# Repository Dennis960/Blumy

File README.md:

# Blumy

- A smart soil moisture sensor

## Project Structure

- [.devcontainer](.devcontainer): Contains the configurations for the devcontainers
- [.github](.github): Contains the configuration for GitHub Actions
- [Board](Board): Contains the KiCad project for the board
- [Panel](Panel): Contains the KiCad project for the board panel. Generation of the panel is done with `KiKit`
- [Firmware](Firmware): Contains the firmware for the esp(32) sensor (uses esp-idf)
- [Pages](Pages): Contains the website for the project's showcase
- [Server](Server): Contains the website for displaying sensor data

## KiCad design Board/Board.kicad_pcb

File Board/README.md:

# This project uses KiCad 7

## Plugins:

- [Fabrication ToolKit](https://github.com/bennymeg/JLC-Plugin-for-KiCad)

## Other software

- [JLC2KiCadLib Downloader](https://github.com/TousstNicolas/JLC2KiCad_lib)
- inside Board run `JLC2KiCadLib C94599 C1525 C1525 C1527 C16780 C15195 C15525 C2297 C81598 C84256 C26082 C25905 C11702 C25744 C4109 C318884 C318884 C2827328 C146233 C6186 C778186 C5736265 C10418 C2997435 -dir lib -model_dir packages3d -footprint_lib CustomFootprints.pretty -symbol_lib_dir symbol -symbol_lib Custom_Parts`

## PCB Manufacturer

- [JLCPCB](https://jlcpcb.com/)

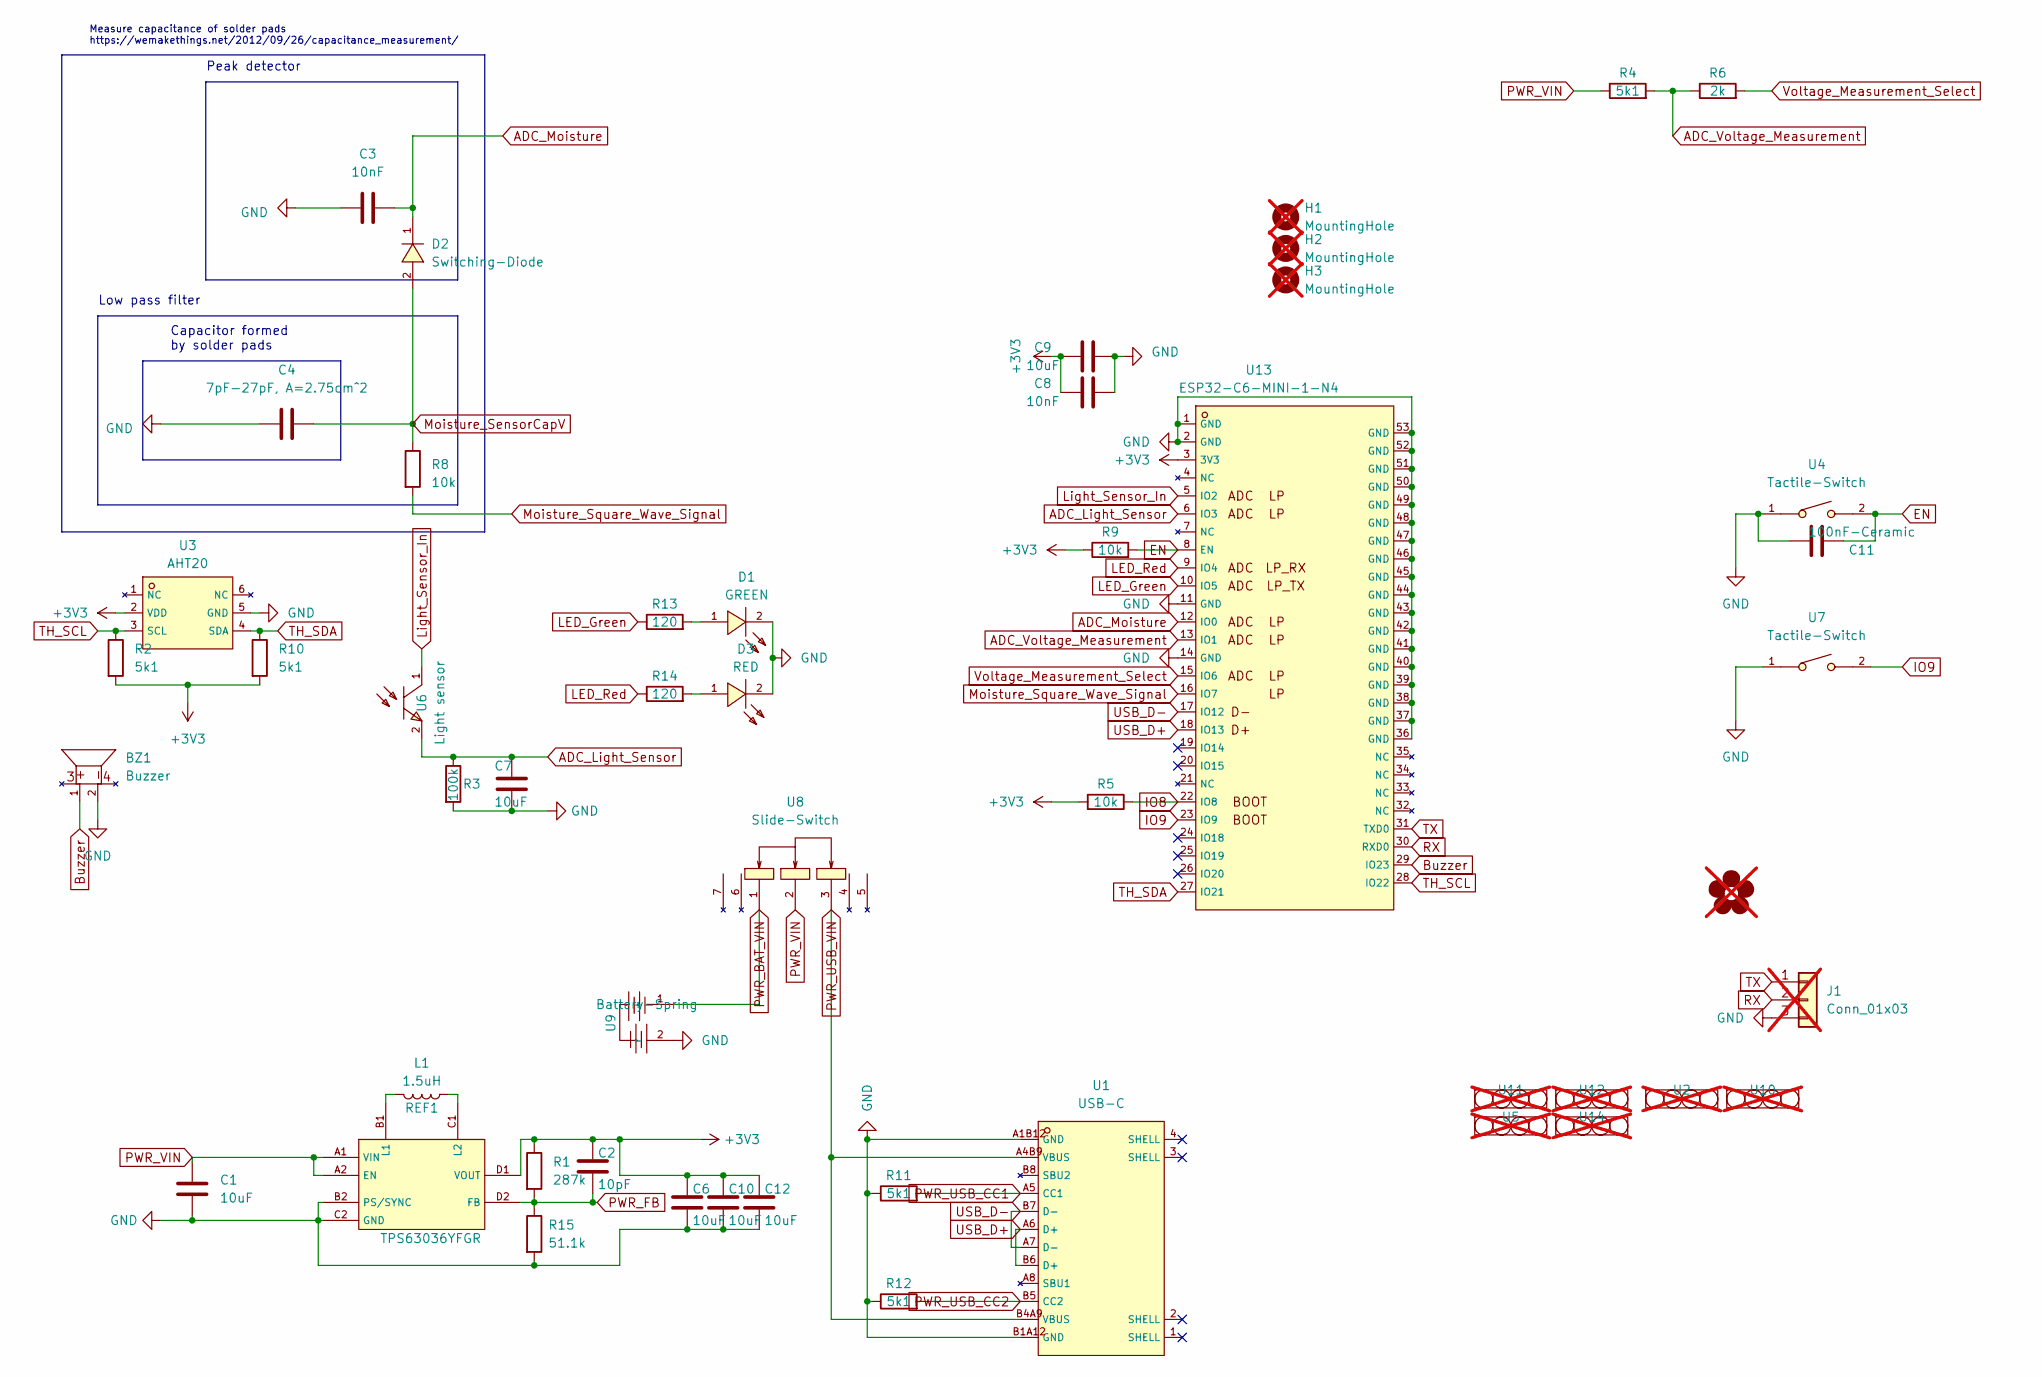
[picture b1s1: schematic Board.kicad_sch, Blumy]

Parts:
BZ1: Buzzer; BUZ-SMD_4P-L8.5-W8.5-P8.50-BR; MPN C94599; LCSC C94599
C1, C6, C7, C9, C10, C12: 10uF; C_0402_1005Metric; MPN C15525; LCSC C15525
C2: 10pF; C_0402_1005Metric; MPN C32949; LCSC C32949
C3, C8: 10nF; C_0402_1005Metric; MPN C15195; LCSC C15195
C4: 7pF-27pF, A=2.75cm^2; Sensor-Tip; MPN /
C11: 100nF-Ceramic; C_0402_1005Metric; MPN C1525; LCSC C1525
D1: GREEN; LED0805-R-RD; MPN C2297; LCSC C2297
D2: Switching-Diode; SOD-123F_L2.7-W1.6-LS3.8-RD; MPN C81598; LCSC C81598
D3: RED; LED0805-R-RD; MPN C84256; LCSC C84256
Flower1: Flower; MPN /; not fitted
H1, H2, H3: MountingHole; MountingHole_3.2mm_M3; MPN /; not fitted
J1: Conn_01x03; PinHeader_1x03_P2.54mm_Vertical_SMD; MPN /; not fitted
L1: 1.5uH; L0806; MPN C668311; LCSC C668311
R1: 287k; R_0402_1005Metric; MPN C321426; LCSC C321426
R2, R4, R10, R11, R12: 5k1; R_0402_1005Metric; MPN C25905; LCSC C25905
R3: 100k; R_0402_1005Metric; MPN C25741; LCSC C25741
R5, R8, R9: 10k; R_0402_1005Metric; MPN C25744; LCSC C25744
R6: 2k; R_0402_1005Metric; MPN C4109; LCSC C4109
R13, R14: 120; R_0402_1005Metric; MPN C25079; LCSC C25079
R15: 51.1k; R_0402_1005Metric; MPN C284602; LCSC C284602
REF1: TPS63036YFGR; DSBGA-8_L1.8-W1.1-R2-C4-P0.40-BR; MPN C283955; LCSC C283955
U1: USB-C; USB-C-SMD_G-SWITCH_GT-USB-7010EN; MPN C2997435; LCSC C2997435
U2, U5, U10, U11, U12, U14: MouseBites5mm; MPN /; not fitted
U3: AHT20; SENSOR-SMD-6_AHT20; MPN C2757850; LCSC C2757850
U4, U7: Tactile-Switch; SW-SMD_L3.9-W3.0-P4.45; MPN C720477; LCSC C720477
U6: Light sensor; SENSORS-SMD_ALS-PT19; MPN C146233; LCSC C146233
U8: Slide-Switch; SW-SMD_MK-12C02-G025; MPN C778186; LCSC C778186
U9: Battery-Spring; AAA Battery-spring; MPN /
U13: ESP32-C6-MINI-1-N4; WIFIM-SMD_61P-L16.6-W13.2-P0.80-ESP32-C6-MINI-1-N4; MPN C5736265; LCSC C5736265

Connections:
+3V3: C2.1, C6.1, C8.1, C9.1, C10.1, C12.1, R1.1, R2.2, R5.2, R9.1, R10.2, REF1.D1 (VOUT), U3.2 (VDD), U13.3 (3V3)
ADC_Light_Sensor: C7.1, R3.1, U6.2 (E), U13.6 (IO3)
ADC_Moisture: C3.2, D2.1 (K), U13.12 (IO0)
ADC_Voltage_Measurement: R4.2, R6.1, U13.13 (IO1)
Buzzer: BZ1.1 (+), U13.29 (IO23)
EN: C11.1, R9.2, U4.2, U13.8 (EN)
GND: BZ1.2, C1.2, C3.1, C4.2, C6.2, C7.2, C8.2, C9.2, C10.2, C11.2, C12.2, D1.2 (K), D3.2 (-), J1.3, R3.2, R11.1, R12.1, R15.2, REF1.B2 (PS/SYNC), REF1.C2 (GND), U1.A1B12 (GND), U1.B1A12 (GND), U3.5 (GND), U4.1, U7.1, U9.2 (-), U13.1 (GND), U13.2 (GND), U13.11 (GND), U13.14 (GND), U13.36 (GND), U13.37 (GND), U13.38 (GND), U13.39 (GND), U13.40 (GND), U13.41 (GND), U13.42 (GND), U13.43 (GND), U13.44 (GND), U13.45 (GND), U13.46 (GND), U13.47 (GND), U13.48 (GND), U13.49 (GND), U13.50 (GND), U13.51 (GND), U13.52 (GND), U13.53 (GND)
IO8: R5.1, U13.22 (IO8)
IO9: U7.2, U13.23 (IO9)
LED_Green: R13.1, U13.10 (IO5)
LED_Red: R14.1, U13.9 (IO4)
Light_Sensor_In: U6.1 (C), U13.5 (IO2)
Moisture_SensorCapV: C4.1, D2.2 (A), R8.1
Moisture_Square_Wave_Signal: R8.2, U13.16 (IO7)
unnamed: D1.1 (A), R13.2
unnamed: D3.1 (+), R14.2
unnamed: L1.2, REF1.B1 (L1)
unnamed: L1.1, REF1.C1 (L2)
PWR_BAT_VIN: U8.1, U9.1 (+)
PWR_FB: C2.2, R1.2, R15.1, REF1.D2 (FB)
PWR_USB_CC1: R11.2, U1.A5 (CC1)
PWR_USB_CC2: R12.2, U1.B5 (CC2)
PWR_USB_VIN: U1.A4B9 (VBUS), U1.B4A9 (VBUS), U8.3
PWR_VIN: C1.1, R4.1, REF1.A1 (VIN), REF1.A2 (EN), U8.2
RX: J1.2, U13.30 (RXD0)
TH_SCL: R2.1, U3.3 (SCL), U13.28 (IO22)
TH_SDA: R10.1, U3.4 (SDA), U13.27 (IO21)
TX: J1.1, U13.31 (TXD0)
USB_D+: U1.A6 (D+), U1.B6 (D+), U13.18 (IO13)
USB_D-: U1.A7 (D-), U1.B7 (D-), U13.17 (IO12)
Voltage_Measurement_Select: R6.2, U13.15 (IO6)

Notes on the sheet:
Capacitor formed by solder pads
Measure capacitance of solder pads https://wemakethings.net/2012/09/26/capacitance_measurement/
Peak detector
Low pass filter

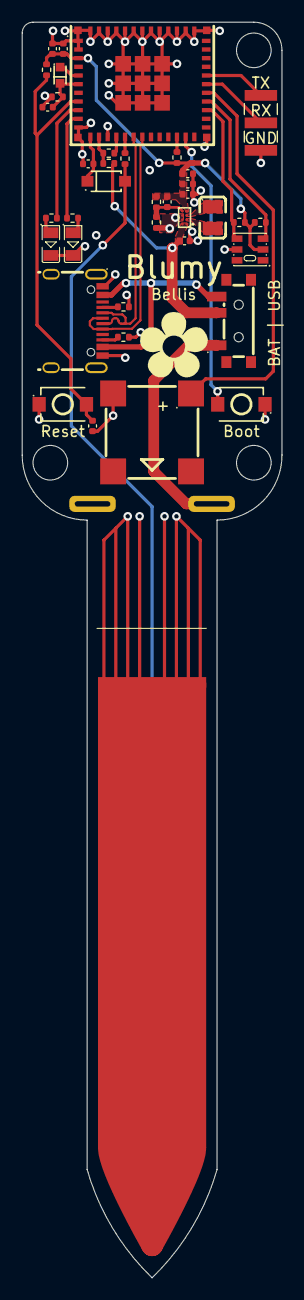
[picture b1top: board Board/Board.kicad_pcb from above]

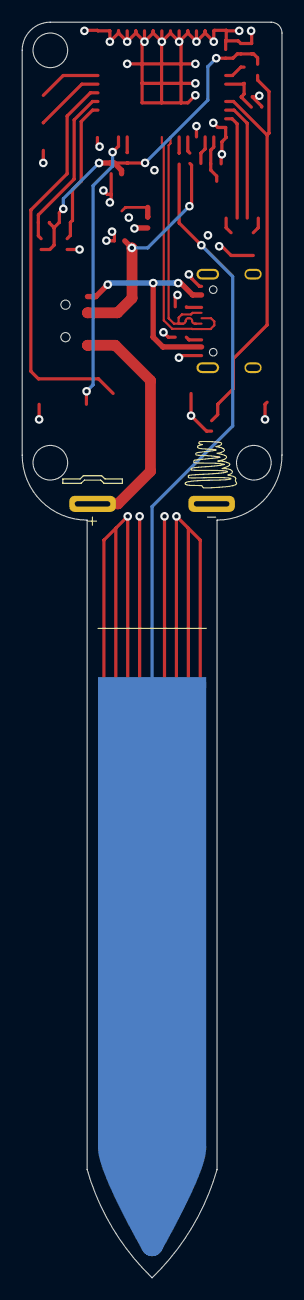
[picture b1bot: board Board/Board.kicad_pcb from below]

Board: 4 copper layers, 24.0 x 116.0 mm, 50 parts (2 on the bottom side), 31 nets.

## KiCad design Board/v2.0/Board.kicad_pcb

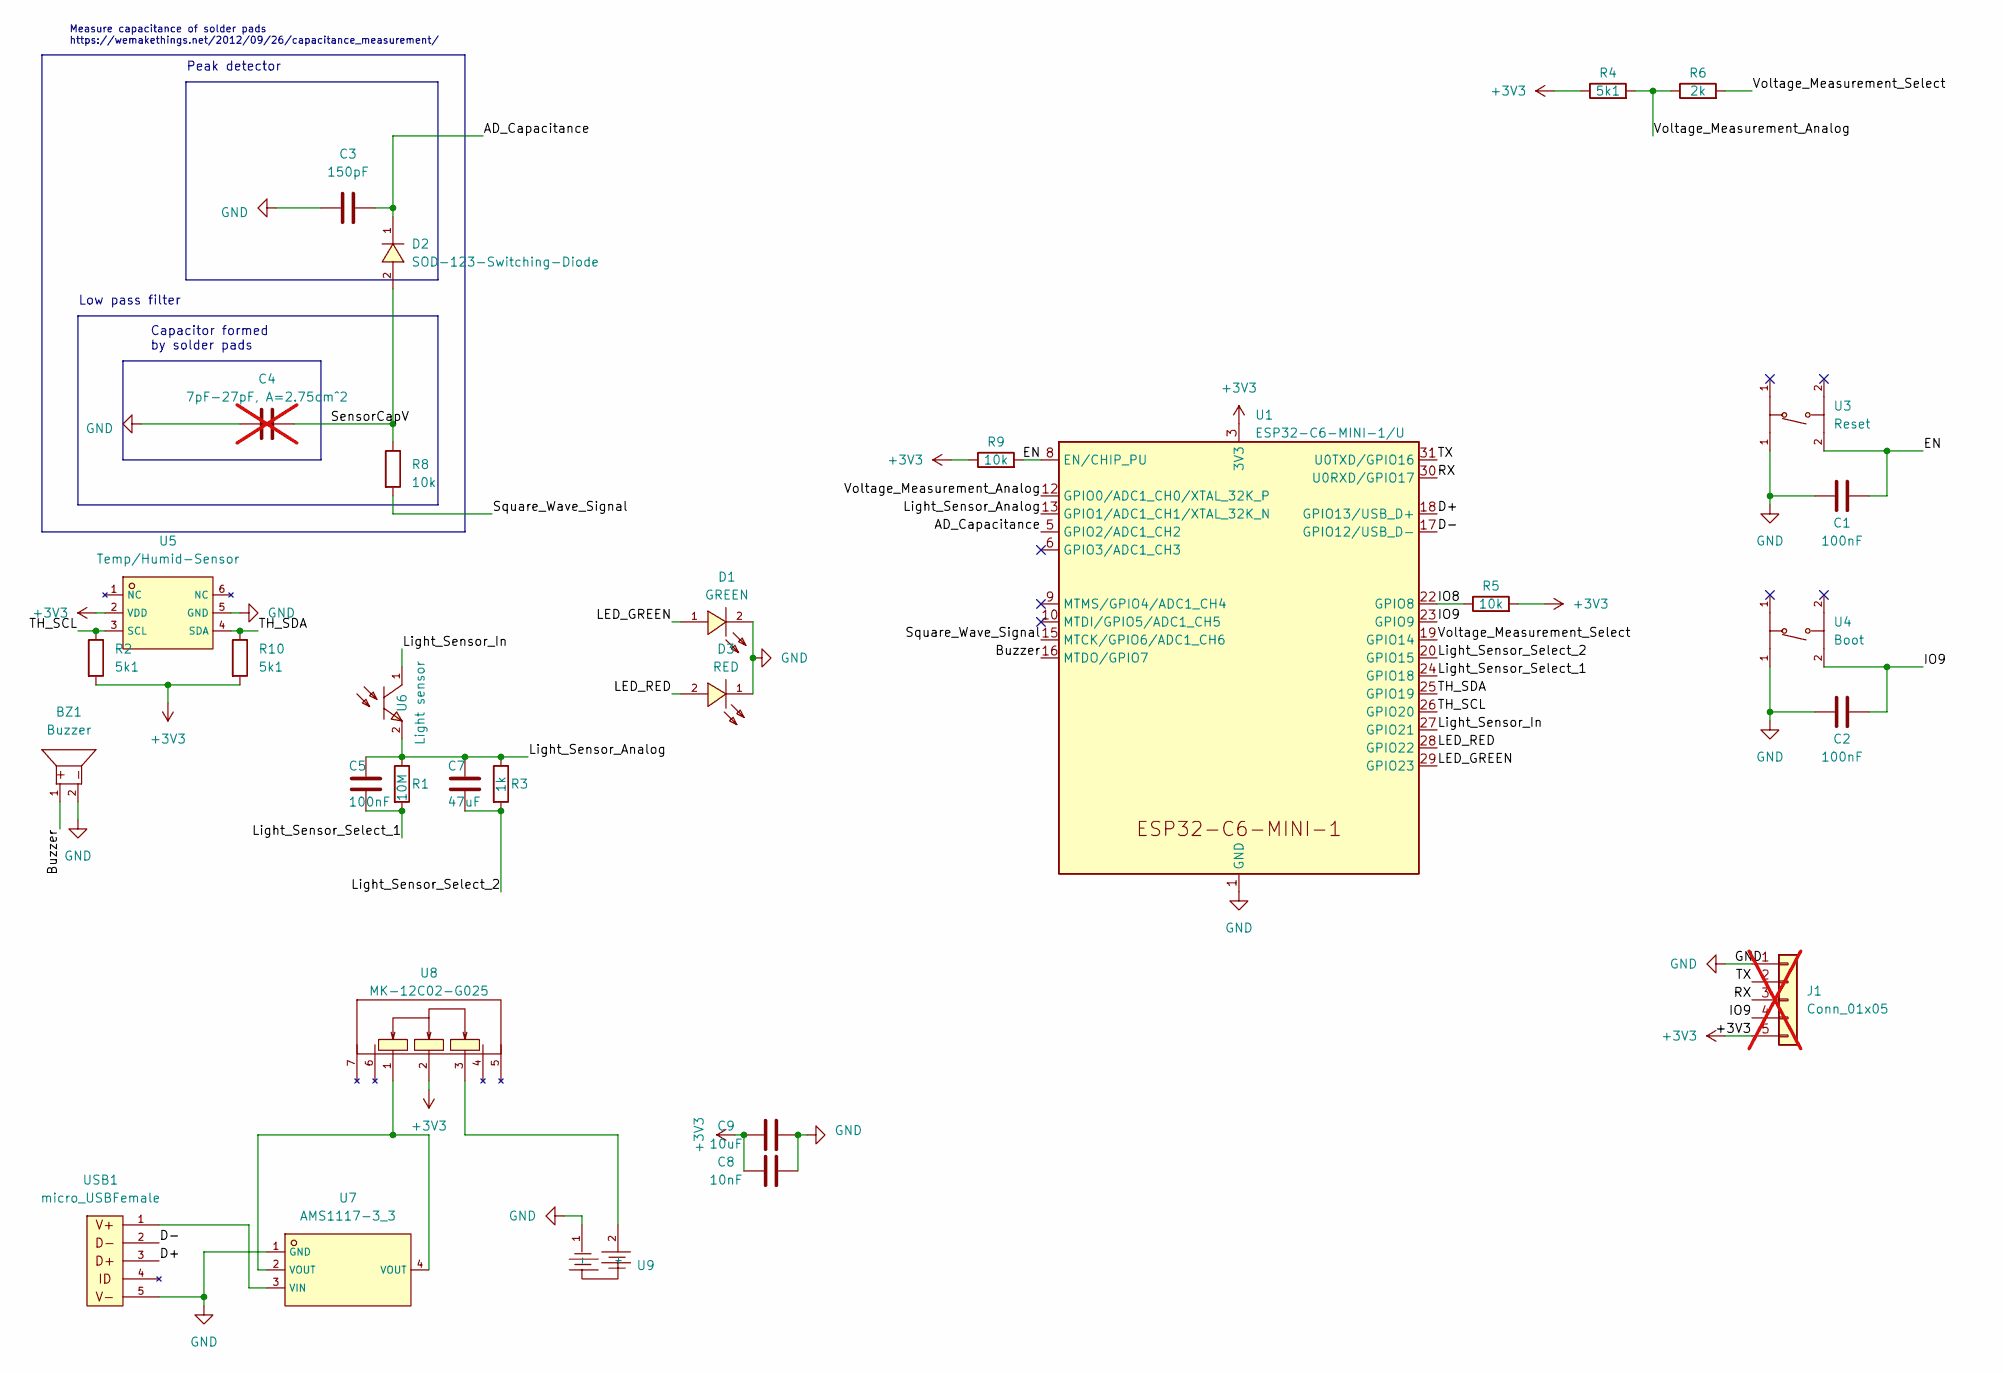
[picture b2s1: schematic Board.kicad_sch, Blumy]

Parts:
BZ1: Buzzer; BUZ-SMD_4P-L8.5-W8.5-P8.50-BR; MPN C94599; LCSC C94599
C1, C2, C5: 100nF; C_0402_1005Metric; MPN C1525; LCSC C1525
C3: 150pF; C_0402_1005Metric; MPN C1527; LCSC C1527
C4: 7pF-27pF, A=2.75cm^2; MPN /; LCSC /; not fitted
C7: 47uF; C_0805_2012Metric; MPN C16780; LCSC C16780
C8: 10nF; C_0402_1005Metric; MPN C15195; LCSC C15195
C9: 10uF; C_0402_1005Metric; MPN C15525; LCSC C15525
D1: GREEN; LED0805-GREEN-RD; MPN C2297; LCSC C2297
D2: SOD-123-Switching-Diode; SOD-123F_L2.7-W1.6-LS3.8-RD; MPN C81598; LCSC C81598
D3: RED; LED0805-RD_RED; MPN C84256; LCSC C84256
J1: Conn_01x05; PinHeader_1x05_P2.54mm_Vertical; MPN /; LCSC /; not fitted
R1: 10M; R_0402_1005Metric; MPN C26082; LCSC C26082
R2, R4, R10: 5k1; R_0402_1005Metric; MPN C25905; LCSC C25905
R3: 1k; R_0402_1005Metric; MPN C11702; LCSC C11702
R5, R8, R9: 10k; R_0402_1005Metric; MPN C25744; LCSC C25744
R6: 2k; R_0402_1005Metric; MPN C4109; LCSC C4109
U1: ESP32-C6-MINI-1/U; ESP32-C6-MINI-1; MPN C5736265; LCSC C5736265
U3: Reset; SW_Push_1P1T_XKB_TS-1187A; MPN C318884; LCSC C318884
U4: Boot; SW_Push_1P1T_XKB_TS-1187A; MPN C318884; LCSC C318884
U5: Temp/Humid-Sensor; SENSOR-SMD_L3.0-W3.0-P1.00-BR; MPN C2827328; LCSC C2827328
U6: Light sensor; SENSORS-SMD_ALS-PT19; MPN C146233; LCSC C146233
U7: AMS1117-3_3; SOT-223-3_L6.5-W3.4-P2.30-LS7.0-BR; MPN C6186; LCSC C6186
U8: MK-12C02-G025; SW-SMD_MK-12C02-G025; MPN C778186; LCSC C778186
U9: AAA Battery-spring; MPN /; LCSC /
USB1: micro_USBFemale; MICRO-USB-SMD_5P-P0.65-H-F_C10418; MPN C10418; LCSC C10418

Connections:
+3V3: C8.1, C9.1, J1.5, R2.2, R4.1, R5.2, R9.1, R10.2, U1.3 (3V3), U5.2 (VDD), U8.2
/AD_Capacitance: C3.2, D2.1 (K), U1.5 (GPIO2/ADC1_CH2)
/Buzzer: BZ1.1 (+), U1.16 (MTDO/GPIO7)
/D+: U1.18 (GPIO13/USB_D+), USB1.3 (D+)
/D-: U1.17 (GPIO12/USB_D-), USB1.2 (D-)
/EN: C1.2, R9.2, U1.8 (EN/CHIP_PU), U3.2 (C)
/IO8: R5.1, U1.22 (GPIO8)
/IO9: C2.2, J1.4, U1.23 (GPIO9), U4.2 (C)
/LED_GREEN: D1.1 (A), U1.29 (GPIO23)
/LED_RED: D3.2 (+), U1.28 (GPIO22)
/Light_Sensor_Analog: C5.1, C7.1, R1.1, R3.1, U1.13 (GPIO1/ADC1_CH1/XTAL_32K_N), U6.2 (E)
/Light_Sensor_In: U1.27 (GPIO21), U6.1 (C)
/Light_Sensor_Select_1: C5.2, R1.2, U1.24 (GPIO18)
/Light_Sensor_Select_2: C7.2, R3.2, U1.20 (GPIO15)
/RX: J1.3, U1.30 (U0RXD/GPIO17)
/SensorCapV: C4.2, D2.2 (A), R8.1
/Square_Wave_Signal: R8.2, U1.15 (MTCK/GPIO6/ADC1_CH6)
/TH_SCL: R2.1, U1.26 (GPIO20), U5.3 (SCL)
/TH_SDA: R10.1, U1.25 (GPIO19), U5.4 (SDA)
/TX: J1.2, U1.31 (U0TXD/GPIO16)
/Voltage_Measurement_Analog: R4.2, R6.1, U1.12 (GPIO0/ADC1_CH0/XTAL_32K_P)
/Voltage_Measurement_Select: R6.2, U1.19 (GPIO14)
GND: BZ1.2, C1.1, C2.1, C3.1, C4.1, C8.2, C9.2, D1.2 (K), D3.1 (-), J1.1, U1.1 (GND), U1.2 (GND), U1.11 (GND), U1.14 (GND), U1.36 (GND), U1.37 (GND), U1.38 (GND), U1.39 (GND), U1.40 (GND), U1.41 (GND), U1.42 (GND), U1.43 (GND), U1.44 (GND), U1.45 (GND), U1.46 (GND), U1.47 (GND), U1.48 (GND), U1.49 (GND), U1.50 (GND), U1.51 (GND), U1.52 (GND), U1.53 (GND), U3.1 (A), U4.1 (A), U5.5 (GND), U7.1 (GND), U9.1 (-), USB1.5 (V-)
unnamed: U7.3 (VIN), USB1.1 (V+)
unnamed: U7.2 (VOUT), U7.4 (VOUT), U8.1
unnamed: U8.3, U9.2 (+)

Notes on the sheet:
Capacitor formed by solder pads
Measure capacitance of solder pads https://wemakethings.net/2012/09/26/capacitance_measurement/
Peak detector
Low pass filter

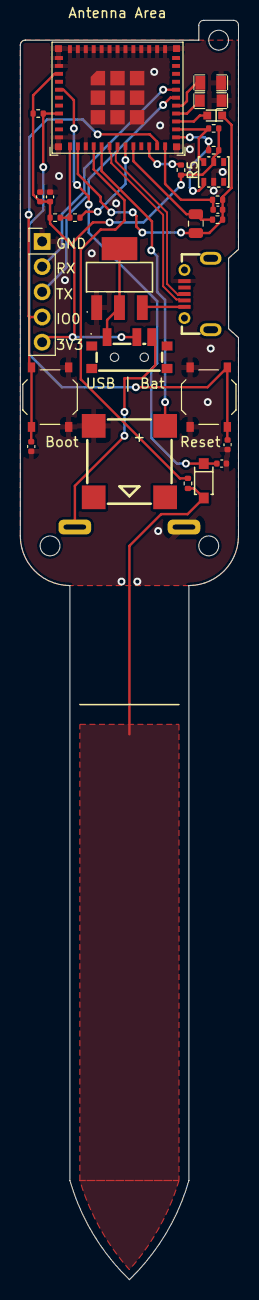
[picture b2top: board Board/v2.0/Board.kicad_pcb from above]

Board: 2 copper layers, 22.0 x 127.0 mm, 30 parts (1 on the bottom side), 26 nets.

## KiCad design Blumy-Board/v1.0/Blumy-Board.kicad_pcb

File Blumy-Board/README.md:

# This project uses KiCad 7

## Plugins:

- [Fabrication ToolKit](https://github.com/bennymeg/JLC-Plugin-for-KiCad)

## Other software

- [JLC2KiCadLib Downloader](https://github.com/TousstNicolas/JLC2KiCad_lib)
- inside Blumy-Board run `JLC2KiCadLib C94599 C1525 C1525 C1527 C16780 C15195 C15525 C2297 C81598 C84256 C26082 C25905 C11702 C25744 C4109 C318884 C318884 C2827328 C146233 C6186 C778186 C5736265 C10418 C2997435 -dir lib -model_dir packages3d -footprint_lib CustomFootprints.pretty -symbol_lib_dir symbol -symbol_lib Custom_Parts`

## PCB Manufacturer

- [JLCPCB](https://jlcpcb.com/)

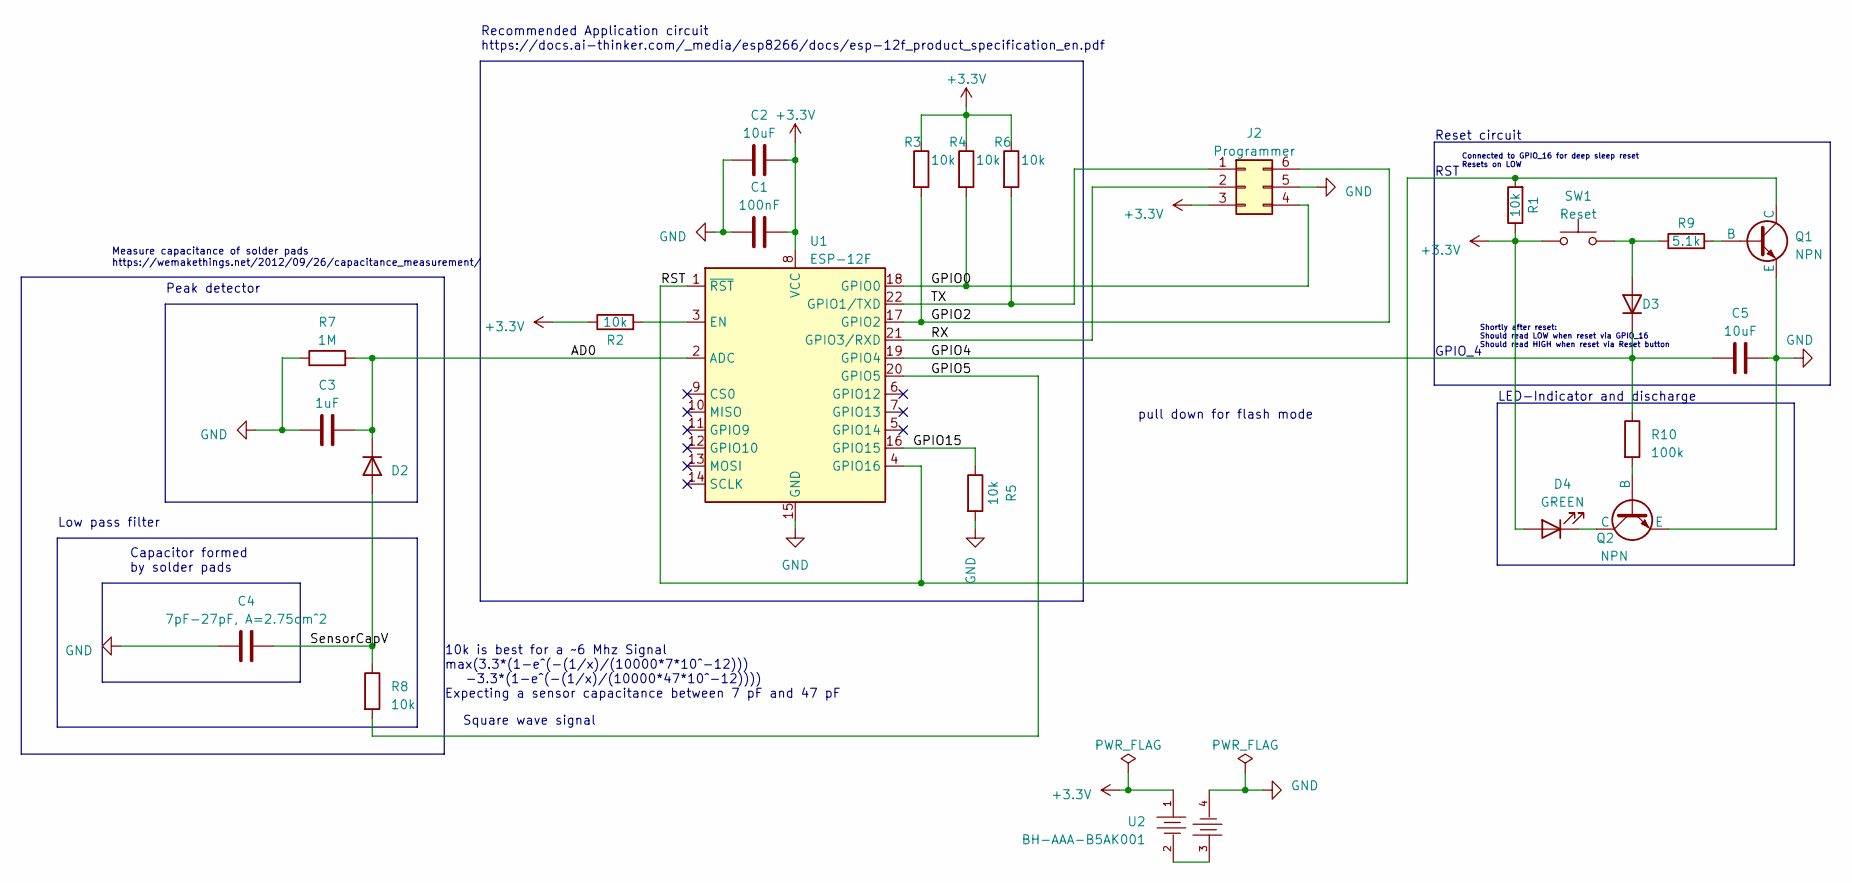
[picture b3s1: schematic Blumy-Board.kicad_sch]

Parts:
C1: 100nF; C_0402_1005Metric; MPN C1525; LCSC C1525
C2, C5: 10uF; C_0402_1005Metric; MPN C15525; LCSC C15525
C3: 1uF; C_0402_1005Metric; MPN C52923; LCSC C52923
C4: 7pF-27pF, A=2.75cm^2
D2, D3: D_SOD-123F; MPN C81598; LCSC C81598
D4: GREEN; LED_0805_2012Metric; MPN C2297; LCSC C2297
J2: Programmer; PinHeader_2x03_P2.54mm_Vertical
Q1, Q2: NPN; SOT-23; MPN C2146; LCSC C2146
R1, R2, R3, R4, R5, R6, R8: 10k; R_0402_1005Metric; MPN C25744; LCSC C25744
R7: 1M; R_0402_1005Metric; MPN C26083; LCSC C26083
R9: 5.1k; R_0402_1005Metric; MPN C25905; LCSC C25905
R10: 100k; R_0402_1005Metric; MPN C25741; LCSC C25741
SW1: Reset; SW_Push_1P1T_XKB_TS-1187A; MPN C318884; LCSC C318884
U1: ESP-12F; ESP-12E; MPN C82891; LCSC C82891
U2: BH-AAA-B5AK001; BAT-SMD_BH-AAA-B5AA001; MPN C964881; LCSC C964881

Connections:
+3.3V: C1.2, C2.2, D4.2 (A), J2.3, R1.1, R2.1, R3.1, R4.1, R6.1, SW1.1, U1.8 (VCC), U2.1 (+)
/AD0: C3.2, D2.1 (K), R7.2, U1.2 (ADC)
/GPIO0: J2.4, R4.2, U1.18 (GPIO0)
/GPIO2: J2.6, R3.2, U1.17 (GPIO2)
/GPIO4: C5.1, D3.1 (K), R10.1, U1.19 (GPIO4)
/GPIO5: R8.2, U1.20 (GPIO5)
/GPIO15: R5.1, U1.16 (GPIO15)
/RST: Q1.1 (C), R1.2, U1.1 (~RST), U1.4 (GPIO16)
/RX: J2.2, U1.21 (GPIO3/RXD)
/SensorCapV: C4.2, D2.2 (A), R8.1
/TX: J2.1, R6.2, U1.22 (GPIO1/TXD)
GND: C1.1, C2.1, C3.1, C4.1, C5.2, J2.5, Q1.3 (E), Q2.3 (E), R5.2, R7.1, U1.15 (GND), U2.4 (-)
unnamed: D3.2 (A), R9.1, SW1.2
unnamed: D4.1 (K), Q2.1 (C)
unnamed: Q1.2 (B), R9.2
unnamed: Q2.2 (B), R10.2
unnamed: R2.2, U1.3 (EN)
unnamed: U2.2 (-), U2.3 (+)

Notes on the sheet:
Capacitor formed by solder pads
Square wave signal
10k is best for a ~6 Mhz Signal max(3.3*(1-e^(-(1/x)/(10000*7*10^-12))) -3.3*(1-e^(-(1/x)/(10000*47*10^-12)))) Expecting a sensor capacitance between 7 pF and 47 pF
Connected to GPIO_16 for deep sleep reset Resets on LOW
Shortly after reset: Should read LOW when reset via GPIO_16 Should read HIGH when reset via Reset button
Recommended Application circuit https://docs.ai-thinker.com/_media/esp8266/docs/esp-12f_product_specification_en.pdf
GPIO_4
Measure capacitance of solder pads https://wemakethings.net/2012/09/26/capacitance_measurement/
Peak detector
RST
pull down for flash mode
Low pass filter
LED-Indicator and discharge
Reset circuit

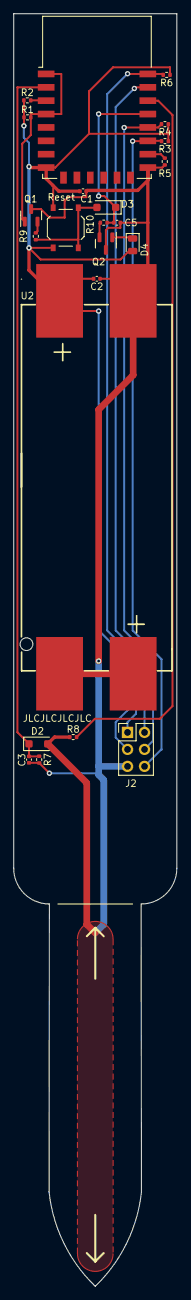
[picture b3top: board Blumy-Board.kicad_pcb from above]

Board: 2 copper layers, 24.4 x 190.2 mm, 23 parts (0 on the bottom side), 18 nets.

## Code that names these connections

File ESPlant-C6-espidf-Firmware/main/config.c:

// ANALOG INPUT
#define ADC_MOISTURE_SENSOR GPIO_NUM_0
#define ADC_MOISTURE_SENSOR_CHANNEL ADC_CHANNEL_0     // GPIO 0, LP
#define ADC_LIGHT_SENSOR_CHANNEL ADC_CHANNEL_3        // GPIO 3, LP
#define ADC_VOLTAGE_MEASUREMENT_CHANNEL ADC_CHANNEL_6 // GPIO 6, LP

// DIGITAL INPUT
#define POWER_USB_VIN GPIO_NUM_15

// DIGITAL OUTPUT
#define LIGHT_SENSOR_IN GPIO_NUM_2             // LP
#define LED_RED GPIO_NUM_4                     // LP
#define LED_GREEN GPIO_NUM_5                   // LP
#define MOISTURE_SQUARE_WAVE_SIGNAL GPIO_NUM_7 // LP
#define BUZZER GPIO_NUM_21

// LEDC CHANNELS
#define BUZZER_CHANNEL LEDC_CHANNEL_0
#define LED_RED_CHANNEL LEDC_CHANNEL_1
#define LED_GREEN_CHANNEL LEDC_CHANNEL_2
#define MOISTURE_SQUARE_WAVE_SIGNAL_CHANNEL LEDC_CHANNEL_3

// DIGITAL INPUT/OUTPUT
#define LIGHT_SENSOR_SELECT GPIO_NUM_1 // LP
#define VOLTAGE_MEASUREMENT_SELECT GPIO_NUM_14

// I2C
#define TEMPERATURE_SENSOR_SDA GPIO_NUM_22
#define TEMPERATURE_SENSOR_SCL GPIO_NUM_23

// USED FOR PROGRAMMING
// #define USB_DM GPIO_NUM_12
// #define USB_DP GPIO_NUM_13
// #define TXD GPIO_NUM_?
// #define RXD GPIO_NUM_?

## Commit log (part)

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2024-04-12 Add debug charts
2024-04-12 Implement battery status UI
2024-04-14 Remove blumy debug
2024-04-14 Firmware: Add sensor logging
2024-04-16 Firmware: Extract wifi and ip handler for better debugging, add shutdown button
2024-04-16 Firmware: Disable Boot Button shutdown
2024-04-16 Firmware: Add comment to disabled boot button
2024-04-20 Board: Add TODO to change regulator
2024-04-27 Board: Change Power Supply Chip
2024-04-27 Board: Remove USB-connected detector
2024-04-27 Fix panel docker
2024-04-27 Panel: Update panel
2024-08-04 Board: Update to V8, add battery springs 3d models
2024-08-17 Casemaker: Delete casemaker (moved to paramecad.com)
2024-08-17 Cleanup
2024-08-17 Implement google oauth route
2024-08-18 Migrate to svelte ssr
2024-08-20 Update create sensor code
2024-08-21 Finishing touches
2024-08-21 Add files needed for deployment
2024-08-23 move test files
2024-08-23 Update dependencies
2024-08-23 Fix playwright tests
2024-08-23 Add playwright reports to github actions
2024-08-23 Move test output path
2024-08-23 Cache
2024-08-23 Add sensor-api tests
2024-08-23 Change database reset order
2024-08-23 Fix tests
2024-08-23 Update github workflows
2024-08-23 Prevent playwright concurrent execution
2024-08-23 Change from static to dynamic env
2024-08-23 Add missing TEST env var to build
2024-08-23 Use github.run_id instead
2024-08-23 only deploy on manual run
2024-08-23 Migrate to sveltekit backend (#23)
2024-08-23 Remove unimplemented deployment environments
2024-08-23 Update docker-compose to work
2024-09-02 Server: Fix eslint problems, add migration script from sqlite to postgres
2024-09-02 Rename project from ESPlant to Blumy
2024-09-02 Rename project from ESPlant to Blumy (#24)
2024-09-02 Update deploy workflow to use correct secrets
2024-09-02 Update docker-compose
2024-09-02 Add differentiation between test mode and production mode
2024-09-02 Automate login, Add logout button
2024-09-02 Fix PUBLIC_MODE env variable
2024-09-03 Update docker compose name
2024-09-03 Fix uploading blumy firmware
2024-09-03 Firmware: Update
2024-09-03 Run tests only when needed
2024-09-03 Fix mistake
2024-09-03 Ignore server certificates
2024-09-03 revert
2024-09-03 Small bugfixes
2024-09-03 Enable ota http
2024-09-03 Add blumy cloud api test endpoint
2024-09-03 Add qol to configuration mode, fix ota update percentage
2024-09-03 Remove Blumy-prefix
2024-09-03 chore: Update Docker image to use kicad/kicad:nightly for board generation
2024-09-03 switch kicad container
2024-09-03 Remove Blumy prefix
2024-09-03 Add prod db restore script
2024-09-03 Fix slider and moisture values
2024-09-04 UX improvements
2024-09-04 Enable dns and nat
2024-09-04 Add blumy cloud automatic configuration
2024-09-05 Add https server to prevent mixed protocol errors
2024-09-05 Improve sensor data preview
2024-09-05 Implement sensor selector page
2024-09-05 Inject cloud setup redirect url from blumy directly
2024-09-05 Fix apiUrl not using https
2024-09-05 Replace api url with http
2024-09-05 Implement login redirect cookie
2024-09-05 Architectural changes
2024-09-05 Implement http and mqtt setup options
2024-09-05 Remove https server because I don't want to have to manage ssl certificates
2024-09-05 Rename finish config button
2024-09-08 Allow to change google account after logout
2024-09-09 Improve sensor setup ux
2024-09-10 Automatically go to next page if auto config is working
2024-09-10 Fix push notifications
2024-09-10 Fix vapid key missing in test-ci
2024-09-10 Make node-cron a normal dependency
2024-09-10 Add database synchronization script
2024-09-11 Add workflow dispatch to server build
2024-09-11 Fix branch selection in deploy workflow
2024-09-11 Remove Superjson
2024-09-11 Fix sensor ota update percentage
2024-09-11 Allow delete sensor
2024-09-12 Add lint rule for security configuration
2024-09-29 Remove ota restart
2024-10-02 Fix sensor link and update delete message
2024-10-02 Set postgres version to 16
2024-10-26 Fix 401 not authenticated when opening share link without account
2025-06-23 Update and fix Board and Panel
2025-06-25 Update Blumy Firmware to use leds and fix configuration bugs
2025-06-25 Update esp idf version
2025-06-25 Fix invalid time error
2025-06-25 Update docker publish job to ubuntu-latest
2025-06-25 Add firmware version and fix led brightness handler
2025-06-25 Add automatic updates and fix factory reset not resetting wifi
2025-06-25 Enable automatic updates
2025-06-25 Fix weird ledc bug
2025-06-26 Add missing tabs to blumy panel
2025-06-26 Reduce ledc calls
2025-06-26 Add captive portal (does not allow google oauth)
2025-06-26 Update github actions
2025-06-26 Update to svelte 5, add username email authentication
2025-06-26 Fix litepicker icons
2025-06-26 Make charts bigger and round values
2025-06-26 Remove credits column
2025-06-26 Fix nouislider css
2025-06-26 Do not run playwright tests twice
2025-06-26 Add option to navigate to sensor from homepage using share link
2025-06-26 Improve and fix styling
2025-06-27 Finish svelte 5 migration
2025-06-27 Remove dbHelper
2025-06-27 Fix href warning
2025-06-27 Refactor api and sensor settings
2025-06-27 Improve login buttons
2025-06-27 Add url and icon to push notifications
2025-06-27 Fix push notification data
2025-06-27 Add missing waitUntil
2025-06-27 Add manifest and ios notification requirements
2025-06-27 Add missing token to notification toggle subscriptions
2025-06-27 Replace flower symbol
2025-06-27 Add default fetch to clientApi
2025-06-27 Add shared sensors section
2025-06-27 Fix table page sorting
2025-06-28 Add mqtt home assistant configuration
2025-06-28 Update blumy setup frontend placeholders
2025-06-28 Fix mqtt test using wrong data
2025-06-28 Use environment variable as firmware version
2025-06-28 Also add firmware.bin file with version number
2025-06-28 Add all firmware.bin files
2025-06-28 Add FirmwareUpdateService
2025-06-28 Add settings page to blumy frontend
2025-06-29 Add blumy homepage, tutorial pages, shop page and waiting list
2025-06-29 Remove console.log
2025-06-29 Fix styling
2025-06-29 Add github link
2025-06-29 Add plausible
2025-06-29 Use route for notification url
2025-07-12 Disable editing of cloud config while making api calls
2025-07-12 Add default values and validation to mqtt form
2025-07-12 Hide aht values in config mode by default
2025-07-12 Fix firmware update message
2025-07-12 Update description of messintervall
2025-07-12 Fix home assistant sensor values
2025-07-12 Fix impressum
2025-07-12 Cleanup devcontainers
2025-07-12 Add READMEs
2025-07-12 Fix voltage configurations, remove isUsbConnected property
2025-07-12 Move defaultSensorConfig
2025-07-12 Fix leds being on during sensor mode bug
2025-07-13 Send notifications when sensor is offline
2025-07-13 Add option to remove shared sensors
2025-07-13 Add tooltips to plant and sensor health icons
2025-07-13 Add 3d model of blumy
2025-07-14 Remove 3d view of Blumy because it causes lag
2025-07-17 Add detection for entering multi configuration mode
2025-07-17 Remove boot capacitor from blumy and flip usb bat text
2025-07-17 Add function to detect type of blumy
2025-07-18 Add unencrypted wifi exchange for multi configuration mode
2025-07-18 Add encryption and frontend to wifi exchange for multi configuration mode
2025-07-18 Specify esp idf version
2025-07-19 Replace contact email
2025-07-19 Only configure ap when needed
2025-07-19 Fix esp crashes with broken aht sensor
2025-07-19 Add blumy host test.
2025-07-20 Create multiconfiguration page
2025-07-20 Fix login modal closes even when login fails
2025-07-20 Update tutorial pages
2025-07-20 Improve selector page loading time
2025-07-20 Fix back to home page button
2025-07-20 Fix spelling
2025-07-20 Fix dhcp configuration
2025-07-20 disable buttons while loading blumy cloud selector page
2025-07-20 Fix Invalid time value bug
2025-07-20 plantdns trying to spoof internet access (not working)
2025-07-20 Fix could not resolve dns after connecting to wifi
2025-07-20 Rename functions
2025-07-20 Fix configuration and ledc warnings
2025-07-23 Add devcontainer port forward
2025-07-23 Fix image rotation bug
2025-07-23 Add option to add multiple sensors via share link and fix double submission bug
2025-07-27 Add sensor navigation arrows
2025-07-27 Remove svelte legacy code from base64 image
2025-07-27 Remove unused css
2025-07-27 Fix sensor capacity history card size
2025-07-27 Refactor code
2025-07-27 Improve dashboard loading time by not prerendering images
2025-07-28 Initial plan
2025-07-28 Add ESP-IDF unit tests for firmware with CI integration
2025-07-28 Fix CI workflow and add test build artifacts to gitignore
2025-07-28 Add comprehensive unit tests for SensorController and API endpoints
2025-07-28 Complete comprehensive testing implementation for selector workflow
2025-07-28 Fix YAML formatting in workflow files
2025-07-28 Fix Playwright E2E tests: configure system Chrome browser and fix database issues
2025-07-28 Fix API authentication in E2E tests and improve FormData handling
2025-07-28 Change water capacity bar colors
2025-07-28 Add touch swipe gestures
2025-07-28 Add wather graph legend
2025-07-28 Make logo navigate to dashboard if use is on subpage of dashboard
2025-07-28 Revert playwright.config.ts changes and create package.json script for Chrome browser
2025-07-28 Fix database schema issues in E2E tests: import eq function and fix foreign key constraints
2025-07-28 Fix authentication redirect behavior for API endpoints
2025-07-28 Fix API authentication status code expectations in tests
2025-07-28 Complete API authentication tests fix - 3/5 tests now passing
2025-07-29 Implement lazy loading of sensor images with separate table
2025-07-29 Replace image url with typesafe clientApi
2025-07-29 Implement lazy loading of sensor images with separate database table (#32)
    * Implement lazy loading of sensor images with separate table
    * Replace image url with typesafe clientApi
    ---------
2025-07-29 Add canEdit property to SensorDTO
2025-07-29 Add eslint types package
2025-07-29 Fix sync-to-prod-db script was not dropping database
2025-07-31 Fix returning null user when accessing through read token
2025-07-31 Fix not being able to change sensor settings
2025-07-31 Fix notification toggle not updating correctly
2025-07-31 update drizzle version
2025-07-31 Move averaging the sensor data to the database query
2025-07-31 Preload previous and next sensor data for more performance
2025-07-31 Fix image rotation and allow image clicks
2025-08-03 Update devcontainer names
2025-08-03 Add image caching
2025-08-03 Show notification toggle even when lastUpdate is undefined
2025-08-03 Allow logo navigation to homepage when on dashboard
2025-08-14 Disable scrolling when updating the date range
2025-09-28 Add image gallery and improve image upload
2025-09-28 Add page titles
2025-09-28 Remove image from sensor api test
2025-09-28 Only show table view for authenticated users
2025-09-28 Add read token to image gallery if needed
2025-09-28 Make new image button same size as other images in gallery
2025-09-28 Update sensor share link text
2025-09-28 Translate funny plant names to german
2025-09-28 Implement feature to allow editing shared sensors
2025-09-28 Fix apexcharts in grid not resizing correctly
2025-09-28 Allow camera or uploading images for sensor image upload input
2025-09-28 Add stored sensors to table view and allow table view for unauthenticated users
2025-11-16 Add blumy case 3d model
2025-11-16 Fix last reading being incorrect because of taking the average
2025-11-16 Fix capacity graph not showing sometimes
2025-11-16 Fix plantfi http fails without internet connection
2025-11-16 Fix unsubscribing unsubscribes from all sensors
2025-11-16 Add notification toggle to table view and dashboard
2026-02-21 Update plausible url
2026-04-04 Minimze docker size
2026-04-11 Aktualisieren von +page.svelte
